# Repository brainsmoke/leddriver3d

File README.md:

# LED Driver for 3D sculptures based on an ESP32 with PSRAM + an STM32F0XX

# Design:

```
   programming &
  micropython REPL
         ||
     .--------.
     |  usb   |
     |   to   |  unified codebase       project specific firmware
     | serial |    /                            \
     '--------'   /                              \
         ||      /   standardized protocol        \
   .--------------.            |                  _____________.--
   |  ESP32-D0WD  |          (UART)              |             |-- multiple LED strands
   |   8M PSRAM   |-- 16bit/color LED frames --> |  STM32F0XX  |-- (temporal dithered)
   |  16M FLASH   |                              |_____________|--
   '--------------'                                            '--

```

# ESP Code `firmware/esp32/`

- Running micropython

- 60 FPS 16bit/color (48bit) animation with some routines written in C for speed.

- Animations use 3D-coordinates of the LEDs, as well as the direction they're pointing at

- Gamma correction & support for multiple LED orderings.

- Cached animation frames to prevent garbage collection hiccups

- Web interface (HTTPS capable, but no automatic cert. updates)

# STM32 Code `firmware/stm32/`

## Protocol

Sending a frame: `( [16 bit brightness]* [ FF FF FF F0 ] )*`

Brightness must be little endian integers in the (inclusive) range `[0 .. 0xFF00]`

`[ FF FF FF F0 ]` is an end of frame marker and allows the protocol to synchronize
in the event of an uneven number of bytes being written to the serial port

The firmware is completely agnostic about the color ordering.

Some of the following firmwares allow for tuning of the pulse interval:

`( [16 bit number]* [ FF FF FF F3 ] )*`

The given number is the number of cycles outputting a byte should take.
(Useful for increasing the FPS and thus improving temporal dithering.

## `dither16.bin`

Read in 16bit/color data in, drive 8 ws2812 LED strips in parallel

## `strip4.bin`

Read in 16bit/color data in, drive 4 ws2812 LED strips in parallel

## `strip5.bin`

Read in 16bit/color data in, drive 5 ws2812 LED strips in parallel,
Supports tuning the pulse interval.

## `relayball.bin`

Read in 16bit/color data in, drive 4 circuit-routed ws2812 LED meshes.
Small LED strands are connected through PADAUK based relay-chips
(`firmware/pdk/relay/`) that use in-band messages to build up routing
circuits.

## `uartball16.bin`

Drives up-to 8 busses with PADAUK based LED drivers which read 38400 baud
uart. `firmware/pdk/softpwm/`

##  `dither8.bin`

Older code using a different input protocol, reads 8bit/color data & transforms this to 16 bit colors
after gamma correction

# STM32 Tester code

## `jitter_timer.bin`

Tester for PADAUK ws2812 relay chips. `firmware/pdk/relay/`

Tests for functionality and measures the clock speed deviation (for binning).

## `timing_experiment.bin`

Dynamically adjust the `T1H` and `T1L` intervals from the ws2812 protocol to
test its limits.

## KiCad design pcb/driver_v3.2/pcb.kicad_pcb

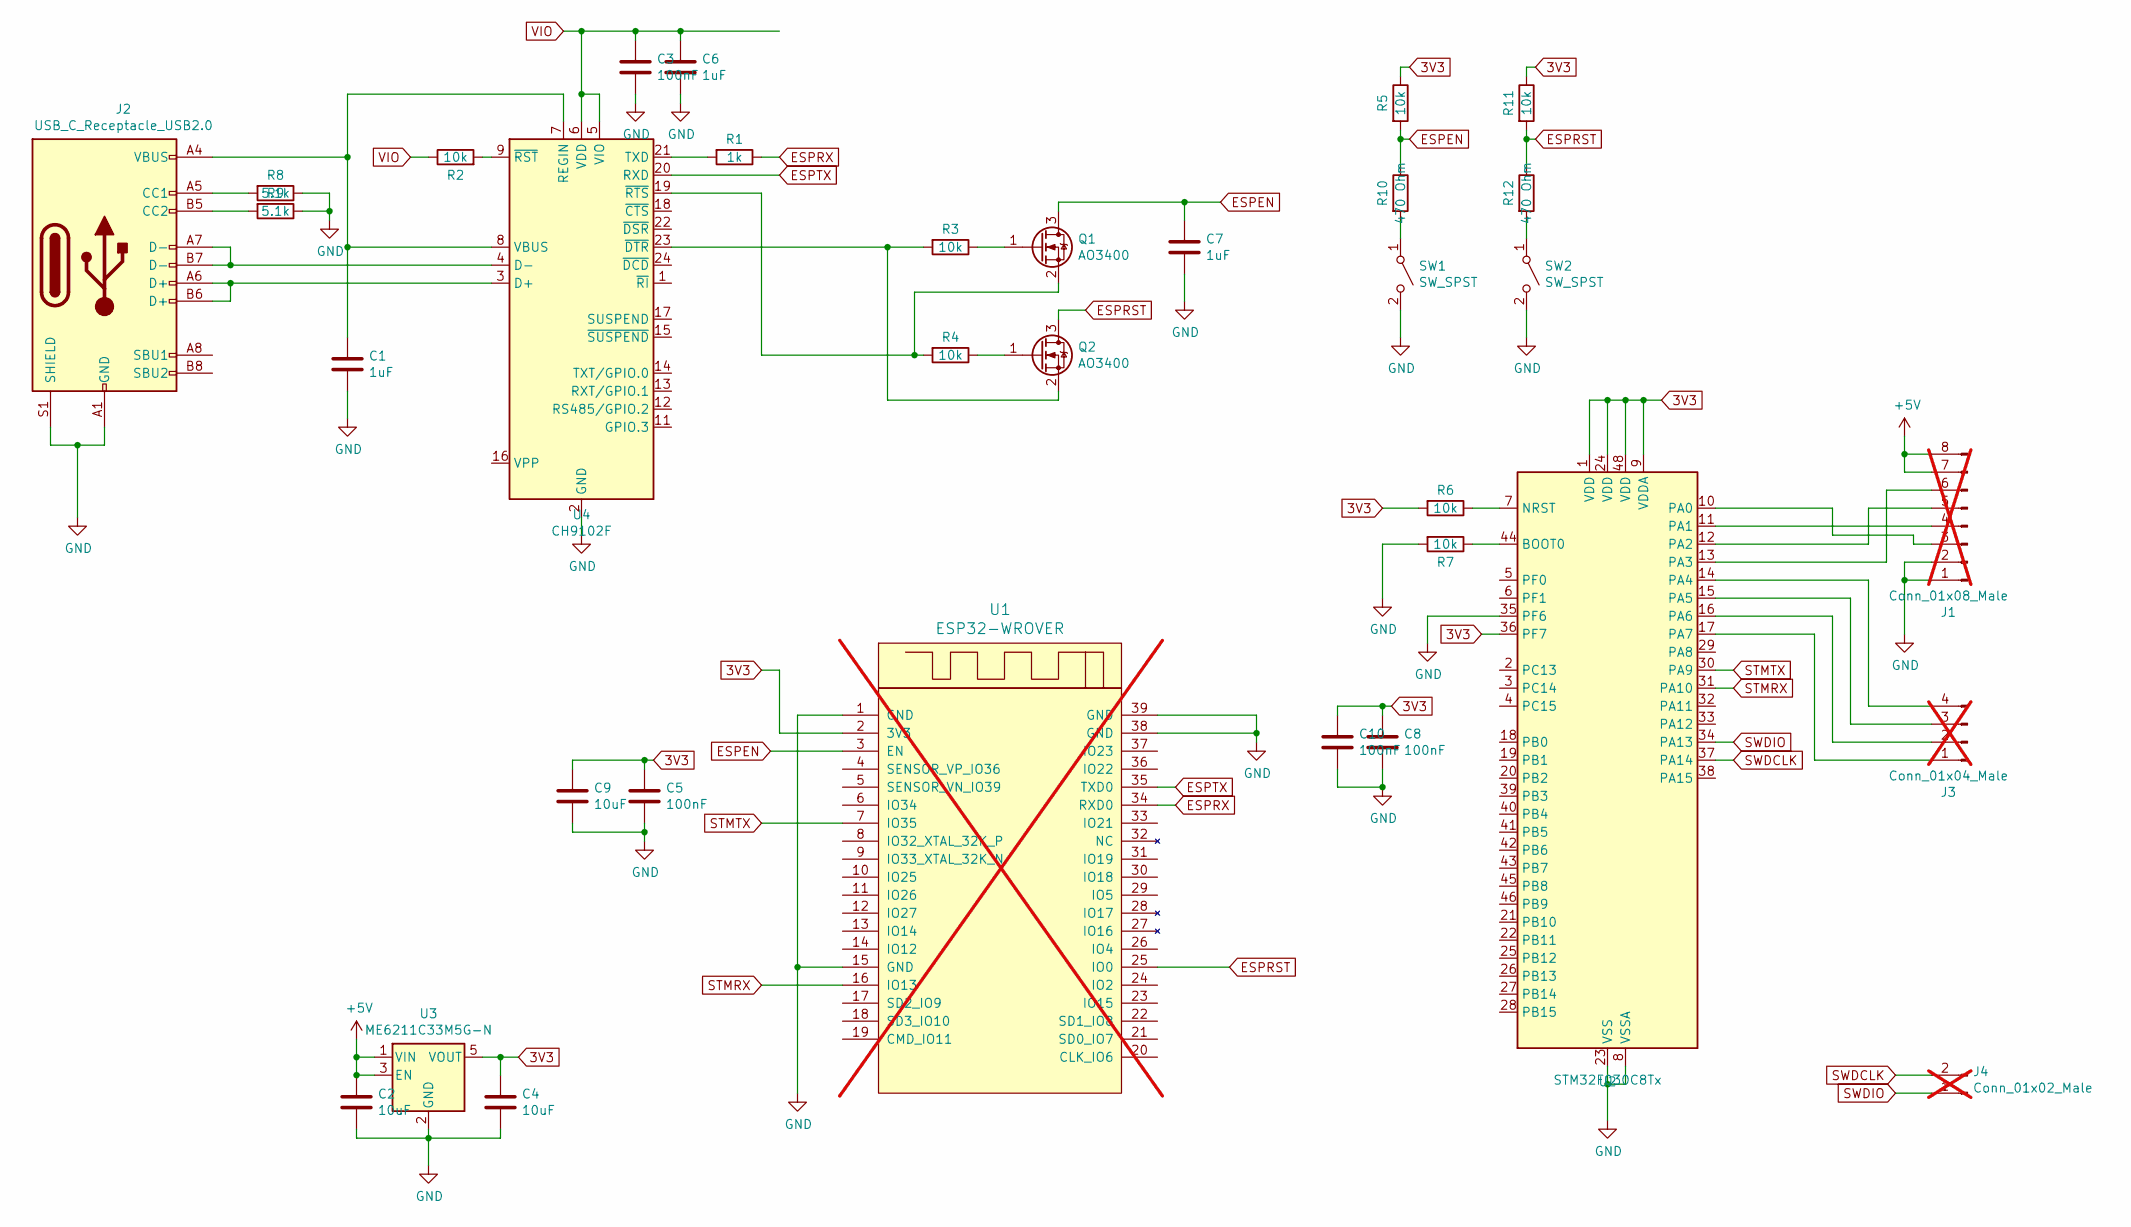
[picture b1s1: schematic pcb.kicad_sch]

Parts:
C1, C6, C7: 1uF; C_0402_1005Metric; LCSC C52923
C2, C4, C9: 10uF; C_0603_1608Metric; LCSC C19702
C3, C5, C8, C10: 100nF; C_0402_1005Metric; LCSC C1525
J1: Conn_01x08_Male; PinHeader_1x08_P2.54mm_Vertical; not fitted
J2: USB_C_Receptacle_USB2.0; USB_C_Receptacle_HRO_TYPE-C-31-M-12; LCSC C165948
J3: Conn_01x04_Male; PinHeader_1x04_P2.54mm_Vertical; not fitted
J4: Conn_01x02_Male; PinHeader_1x02_P2.54mm_Vertical; not fitted
Q1, Q2: AO3400; SOT-23; LCSC C20917
R1: 1k; R_0402_1005Metric; LCSC C11702
R2, R3, R4, R5, R6, R7, R11: 10k; R_0402_1005Metric; LCSC C25744
R8, R9: 5.1k; R_0402_1005Metric; LCSC C25905
R10, R12: 470 Ohm; R_0402_1005Metric; LCSC C25117
SW1, SW2: SW_SPST; SW_Push_1P1T_NO_CK_KMR2; LCSC C318893
U1: ESP32-WROVER; XCVR_ESP32-WROVER; not fitted
U2: STM32F030C8Tx; LQFP-48_7x7mm_P0.5mm; LCSC C23922
U3: ME6211C33M5G-N; SOT-23-5; LCSC C82942
U4: CH9102F; QFN-24-1EP_4x4mm_P0.5mm_EP2.6x2.6mm; LCSC C2858418

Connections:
3V3: C4.1, C5.1, C8.1, C9.1, C10.1, R5.1, R6.2, R11.1, U1.2 (3V3), U2.1 (VDD), U2.9 (VDDA), U2.24 (VDD), U2.36 (PF7), U2.48 (VDD), U3.5 (VOUT)
+5V: C2.1, J1.7, J1.8, U3.1 (VIN), U3.3 (EN)
ESPEN: C7.1, Q1.3 (D), R5.2, R10.1, U1.3 (EN)
ESPRST: Q2.3 (D), R11.2, R12.1, U1.25 (IO0)
ESPRX: R1.1, U1.34 (RXD0)
ESPTX: U1.35 (TXD0), U4.20 (RXD)
GND: C1.2, C2.2, C3.2, C4.2, C5.2, C6.2, C7.2, C8.2, C9.2, C10.2, J1.1, J1.2, J2.A1 (GND), J2.A12 (GND), J2.B1 (GND), J2.B12 (GND), J2.S1 (SHIELD), R7.2, R8.1, R9.1, SW1.2 (B), SW2.2 (B), U1.1 (GND), U1.15 (GND), U1.38 (GND), U1.39 (GND), U2.8 (VSSA), U2.23 (VSS), U2.35 (PF6), U2.47 (VSS), U3.2 (GND), U4.2 (GND), U4.25 (GND)
unnamed: J1.3, U2.10 (PA0)
unnamed: J1.4, U2.11 (PA1)
unnamed: J1.5, U2.12 (PA2)
unnamed: J1.6, U2.13 (PA3)
unnamed: J2.A5 (CC1), R8.2
unnamed: J2.B5 (CC2), R9.2
unnamed: J3.1, U2.17 (PA7)
unnamed: J3.2, U2.16 (PA6)
unnamed: J3.3, U2.15 (PA5)
unnamed: J3.4, U2.14 (PA4)
unnamed: Q1.1 (G), R3.1
unnamed: Q1.2 (S), R4.2, U4.19 (~RTS)
unnamed: Q2.1 (G), R4.1
unnamed: Q2.2 (S), R3.2, U4.23 (~DTR)
unnamed: R10.2, SW1.1 (A)
unnamed: R12.2, SW2.1 (A)
unnamed: R7.1, U2.44 (BOOT0)
unnamed: R6.1, U2.7 (NRST)
unnamed: J2.A6 (D+), J2.B6 (D+), U4.3 (D+)
unnamed: J2.A7 (D-), J2.B7 (D-), U4.4 (D-)
unnamed: C1.1, J2.A4 (VBUS), J2.A9 (VBUS), J2.B4 (VBUS), J2.B9 (VBUS), U4.7 (REGIN), U4.8 (VBUS)
unnamed: R1.2, U4.21 (TXD)
unnamed: R2.2, U4.9 (~RST)
STMRX: U1.16 (IO13), U2.31 (PA10)
STMTX: U1.7 (IO35), U2.30 (PA9)
SWDCLK: J4.2, U2.37 (PA14)
SWDIO: J4.1, U2.34 (PA13)
VIO: C3.1, C6.1, R2.1, U4.5 (VIO), U4.6 (VDD)

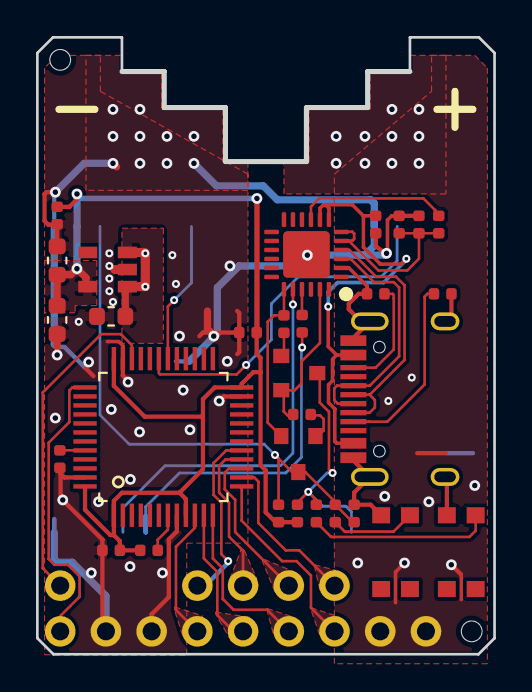
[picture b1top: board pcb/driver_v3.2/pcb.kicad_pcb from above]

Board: 4 copper layers, 25.4 x 34.3 mm, 34 parts (1 on the bottom side), 35 nets.

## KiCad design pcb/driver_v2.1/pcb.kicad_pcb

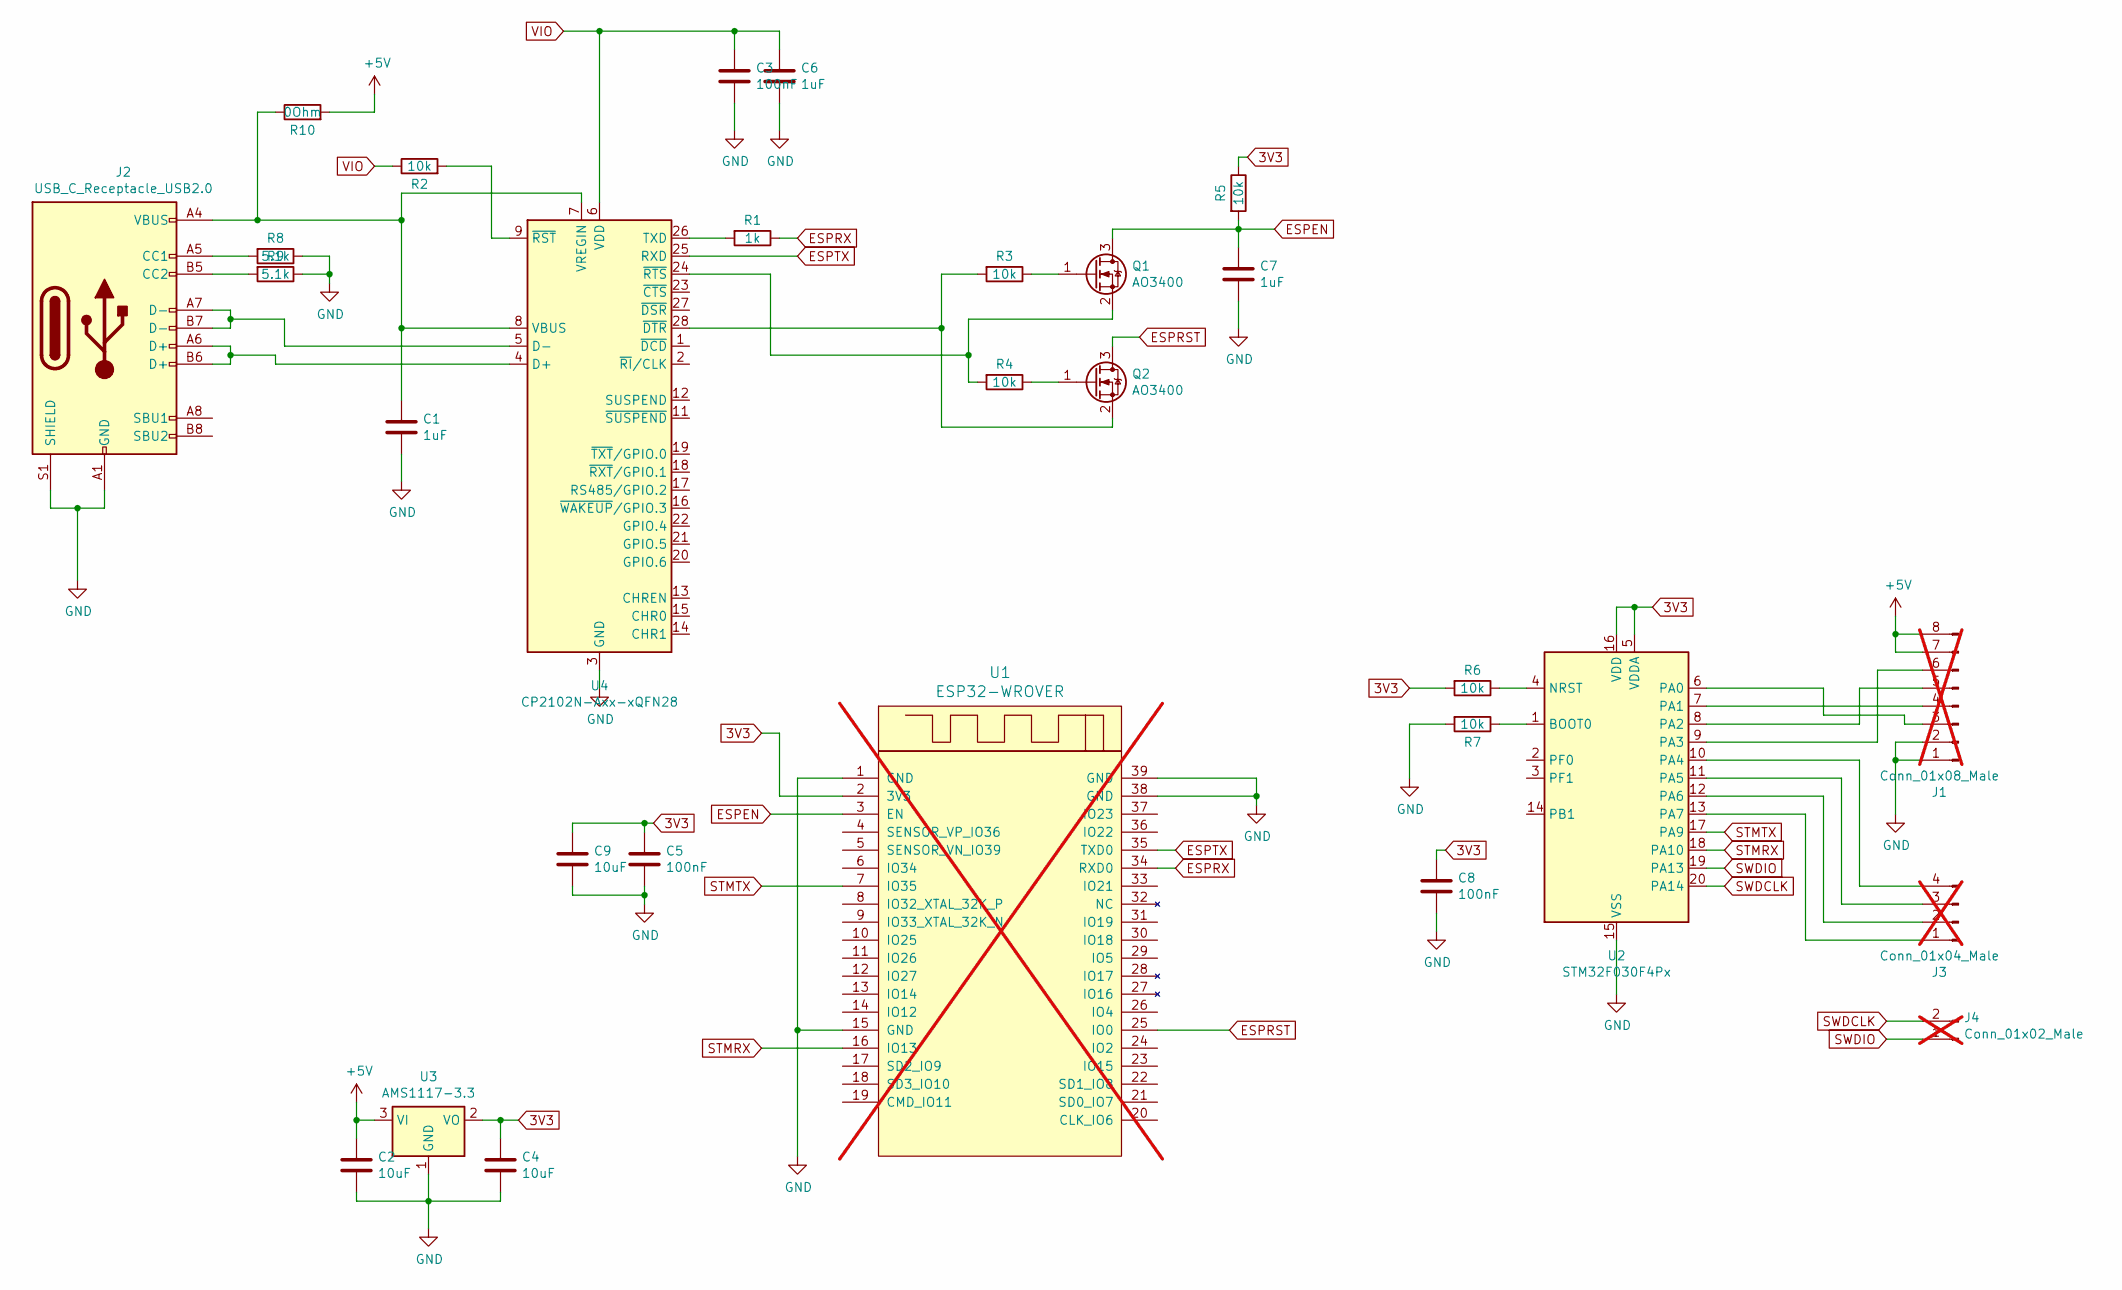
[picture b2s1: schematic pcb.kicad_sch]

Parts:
C1, C6, C7: 1uF; C_0603_1608Metric; LCSC C15849
C2, C4: 10uF; C_0603_1608Metric; LCSC C15850
C3, C5, C8: 100nF; C_0603_1608Metric; LCSC C14663
C9: 10uF; C_0603_1608Metric; LCSC C19702
J1: Conn_01x08_Male; PinHeader_1x08_P2.54mm_Vertical; not fitted
J2: USB_C_Receptacle_USB2.0; USB_C_Receptacle_HRO_TYPE-C-31-M-12; LCSC C165948
J3: Conn_01x04_Male; PinHeader_1x04_P2.54mm_Vertical; not fitted
J4: Conn_01x02_Male; PinHeader_1x02_P2.54mm_Vertical; not fitted
Q1, Q2: AO3400; SOT-23; LCSC C20917
R1: 1k; R_0603_1608Metric_nolabel; LCSC C21190
R2, R3, R4, R5, R6, R7: 10k; R_0603_1608Metric_nolabel; LCSC C25804
R8, R9: 5.1k; R_0603_1608Metric_nolabel; LCSC C23186
R10: 0Ohm; R_0603_1608Metric_nolabel; LCSC C25804
U1: ESP32-WROVER; XCVR_ESP32-WROVER; not fitted
U2: STM32F030F4Px; TSSOP-20_4.4x6.5mm_P0.65mm; LCSC C89040
U3: AMS1117-3.3; SOT-223-3_TabPin2; LCSC C6186
U4: CP2102N-Axx-xQFN28; QFN-28-1EP_5x5mm_P0.5mm_EP3.35x3.35mm; LCSC C6568

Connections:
3V3: C4.1, C5.1, C8.1, C9.1, R5.1, R6.2, U1.2 (3V3), U2.5 (VDDA), U2.16 (VDD), U3.2 (VO)
+5V: C2.1, J1.7, J1.8, R10.2, U3.3 (VI)
ESPEN: C7.1, Q1.3 (D), R5.2, U1.3 (EN)
ESPRST: Q2.3 (D), U1.25 (IO0)
ESPRX: R1.1, U1.34 (RXD0)
ESPTX: U1.35 (TXD0), U4.25 (RXD)
GND: C1.2, C2.2, C3.2, C4.2, C5.2, C6.2, C7.2, C8.2, C9.2, J1.1, J1.2, J2.A1 (GND), J2.A12 (GND), J2.B1 (GND), J2.B12 (GND), J2.S1 (SHIELD), R7.2, R8.1, R9.1, U1.1 (GND), U1.15 (GND), U1.38 (GND), U1.39 (GND), U2.15 (VSS), U3.1 (GND), U4.3 (GND), U4.29 (GND)
unnamed: J1.3, U2.6 (PA0)
unnamed: J1.4, U2.7 (PA1)
unnamed: J1.5, U2.8 (PA2)
unnamed: J1.6, U2.9 (PA3)
unnamed: J2.A5 (CC1), R8.2
unnamed: J2.B5 (CC2), R9.2
unnamed: J3.1, U2.13 (PA7)
unnamed: J3.2, U2.12 (PA6)
unnamed: J3.3, U2.11 (PA5)
unnamed: J3.4, U2.10 (PA4)
unnamed: Q1.1 (G), R3.1
unnamed: Q1.2 (S), R4.2, U4.24 (~RTS)
unnamed: Q2.1 (G), R4.1
unnamed: Q2.2 (S), R3.2, U4.28 (~DTR)
unnamed: R7.1, U2.1 (BOOT0)
unnamed: R6.1, U2.4 (NRST)
unnamed: J2.A6 (D+), J2.B6 (D+), U4.4 (D+)
unnamed: J2.A7 (D-), J2.B7 (D-), U4.5 (D-)
unnamed: R1.2, U4.26 (TXD)
unnamed: C1.1, J2.A4 (VBUS), J2.A9 (VBUS), J2.B4 (VBUS), J2.B9 (VBUS), R10.1, U4.7 (VREGIN), U4.8 (VBUS)
unnamed: R2.2, U4.9 (~RST)
STMRX: U1.16 (IO13), U2.18 (PA10)
STMTX: U1.7 (IO35), U2.17 (PA9)
SWDCLK: J4.2, U2.20 (PA14)
SWDIO: J4.1, U2.19 (PA13)
VIO: C3.1, C6.1, R2.1, U4.6 (VDD)

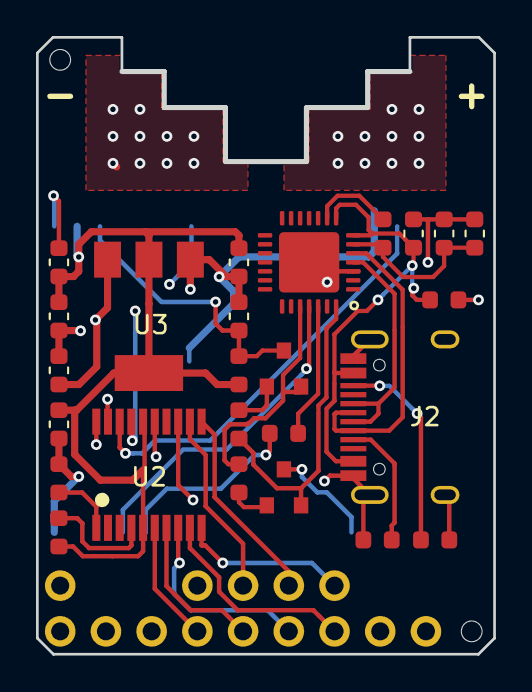
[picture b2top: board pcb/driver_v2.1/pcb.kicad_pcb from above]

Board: 4 copper layers, 25.4 x 34.3 mm, 29 parts (1 on the bottom side), 33 nets.

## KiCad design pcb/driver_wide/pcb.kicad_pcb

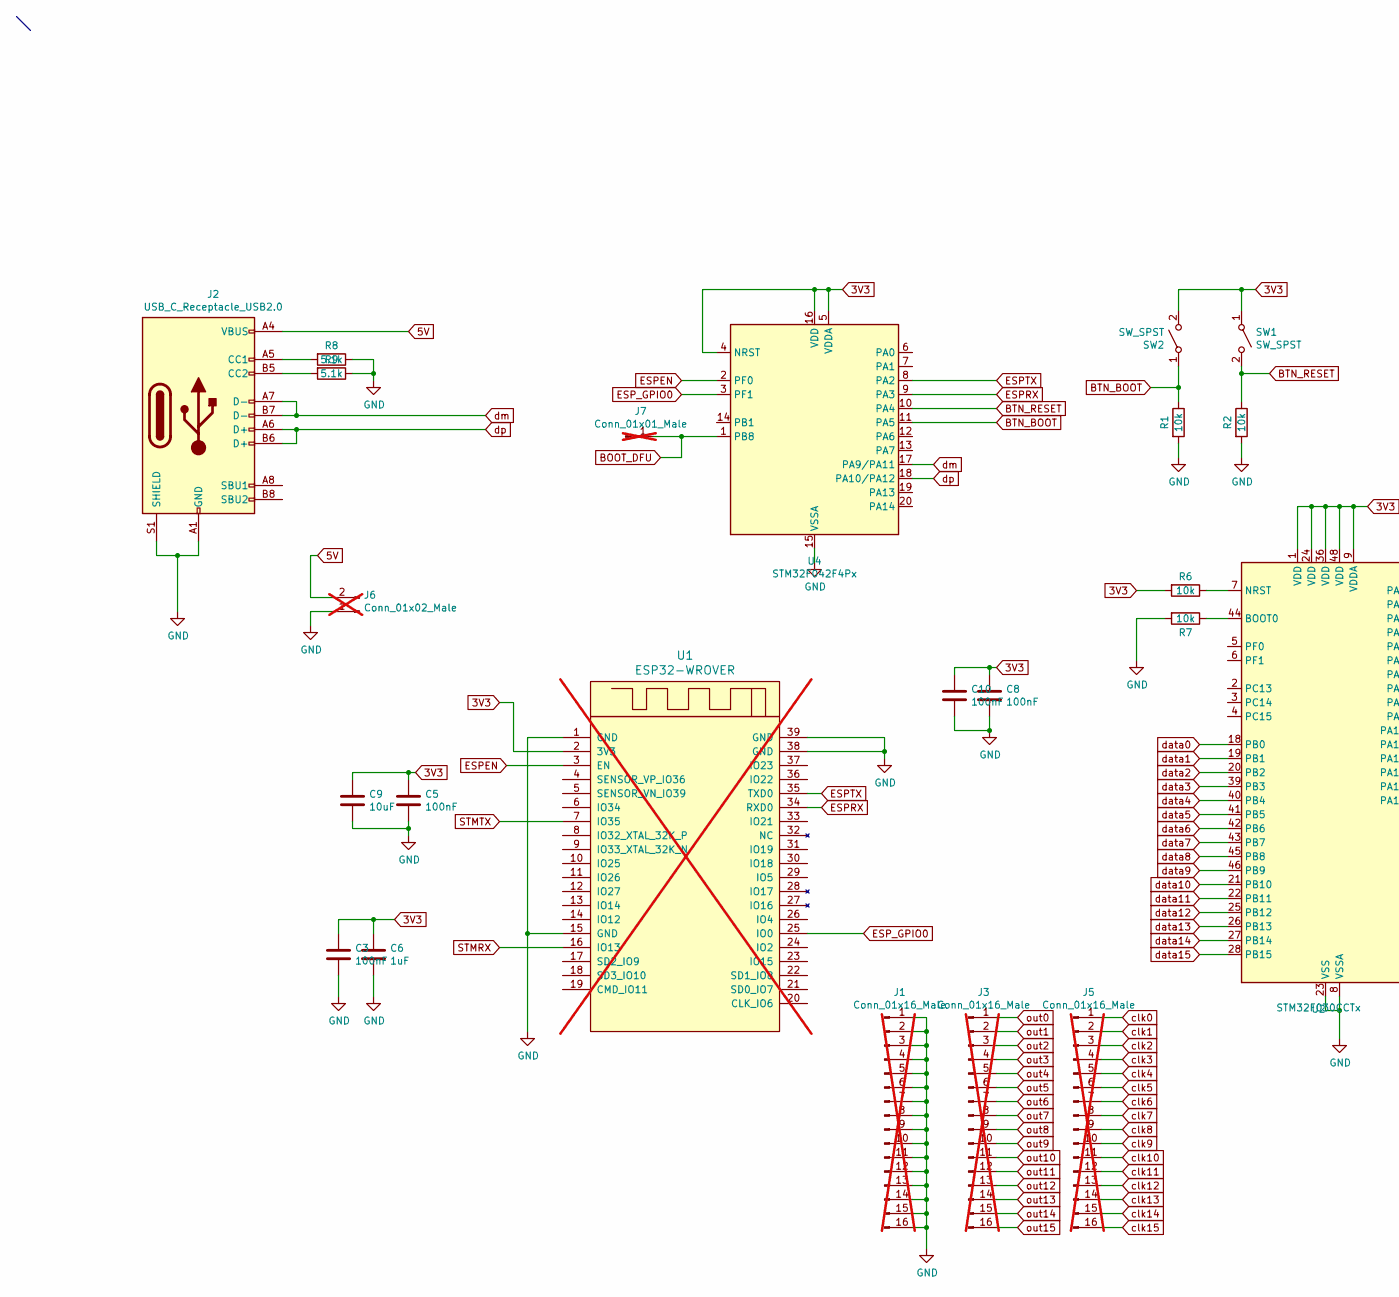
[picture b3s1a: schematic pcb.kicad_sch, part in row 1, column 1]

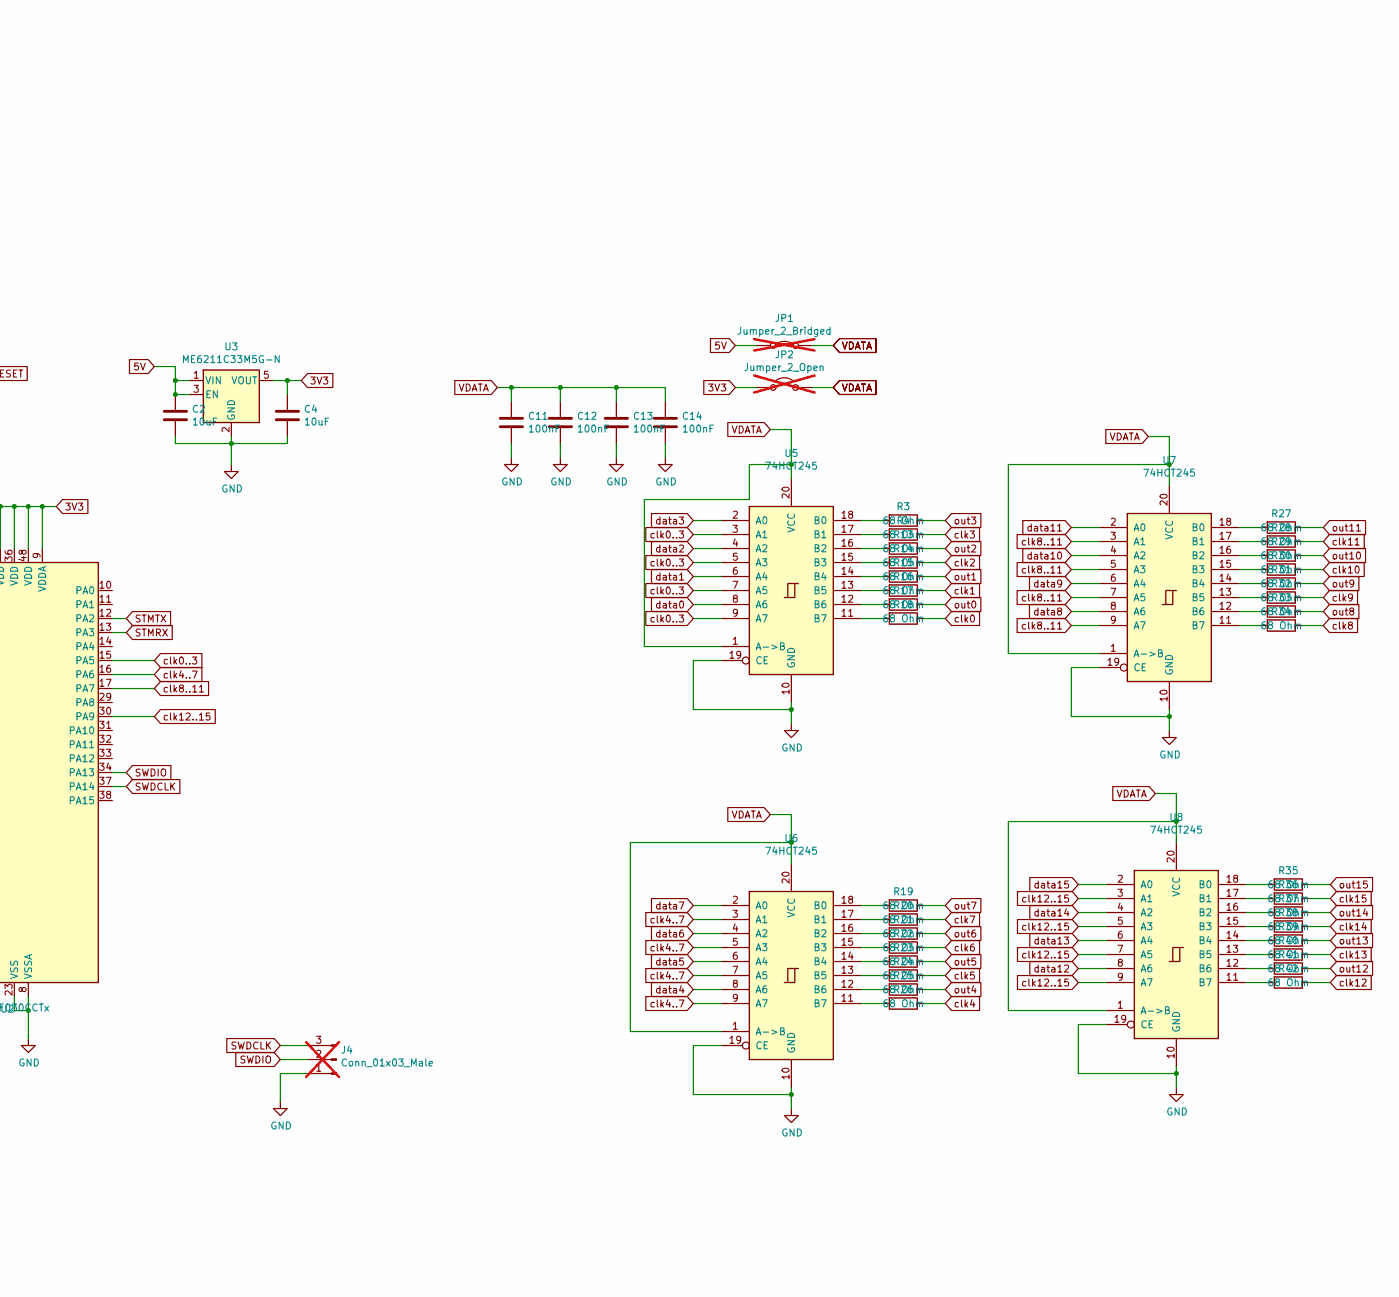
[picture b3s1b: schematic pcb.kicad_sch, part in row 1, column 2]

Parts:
C2, C4, C9: 10uF; C_0603_1608Metric; LCSC C19702
C3, C5, C8, C10: 100nF; C_0402_1005Metric; LCSC C1525
C6: 1uF; C_0402_1005Metric; LCSC C52923
C11, C12, C13, C14: 100nF; C_0402_1005Metric; LCSC C19702
J1, J3, J5: Conn_01x16_Male; PinHeader_1x16_P2.54mm_Vertical; not fitted
J2: USB_C_Receptacle_USB2.0; USB_C_Receptacle_HRO_TYPE-C-31-M-12; LCSC C165948
J4: Conn_01x03_Male; PinHeader_1x03_P2.54mm_Vertical; not fitted
J6: Conn_01x02_Male; PinHeader_1x02_P2.54mm_Vertical; not fitted
J7: Conn_01x01_Male; PinHeader_1x01_P2.54mm_Vertical; not fitted
JP1: Jumper_2_Bridged; SolderJumper-2_P1.3mm_Bridged_Pad1.0x1.5mm; not fitted
JP2: Jumper_2_Open; SolderJumper-2_P1.3mm_Open_Pad1.0x1.5mm; not fitted
R1, R2, R6, R7: 10k; R_0402_1005Metric; LCSC C25744
R3, R4, R13, R14, R15, R16, R17, R18, R19, R20, R21, R22, R23, R24, R25, R26, R27, R28, R29, R30, R31, R32, R33, R34, R35, R36, R37, R38, R39, R40, R41, R42: 68 Ohm; R_0402_1005Metric; LCSC C25744
R8, R9: 5.1k; R_0402_1005Metric; LCSC C25905
SW1, SW2: SW_SPST; SW_Push_1P1T_NO_CK_KMR2; LCSC C318893
U1: ESP32-WROVER; XCVR_ESP32-WROVER; not fitted
U2: STM32F030CCTx; LQFP-48_7x7mm_P0.5mm; LCSC C81787
U3: ME6211C33M5G-N; SOT-23-5; LCSC C82942
U4: STM32F042F4Px; TSSOP-20_4.4x6.5mm_P0.65mm; LCSC C81000
U5, U6, U7, U8: 74HCT245; TSSOP-20_4.4x6.5mm_P0.65mm; LCSC C5980

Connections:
3V3: C3.1, C4.1, C5.1, C6.1, C8.1, C9.1, C10.1, JP2.1 (A), R6.2, SW1.1 (A), SW2.2 (B), U1.2 (3V3), U2.1 (VDD), U2.9 (VDDA), U2.24 (VDD), U2.36 (VDD), U2.48 (VDD), U3.5 (VOUT), U4.4 (NRST), U4.5 (VDDA), U4.16 (VDD)
5V: C2.1, J2.A4 (VBUS), J2.A9 (VBUS), J2.B4 (VBUS), J2.B9 (VBUS), J6.2, JP1.1 (A), U3.1 (VIN), U3.3 (EN)
BOOT_DFU: J7.1, U4.1 (PB8)
BTN_BOOT: R1.1, SW2.1 (A), U4.11 (PA5)
BTN_RESET: R2.1, SW1.2 (B), U4.10 (PA4)
ESPEN: U1.3 (EN), U4.2 (PF0)
ESPRX: U1.34 (RXD0), U4.9 (PA3)
ESPTX: U1.35 (TXD0), U4.8 (PA2)
ESP_GPIO0: U1.25 (IO0), U4.3 (PF1)
GND: C2.2, C3.2, C4.2, C5.2, C6.2, C8.2, C9.2, C10.2, C11.2, C12.2, C13.2, C14.2, J1.1, J1.2, J1.3, J1.4, J1.5, J1.6, J1.7, J1.8, J1.9, J1.10, J1.11, J1.12, J1.13, J1.14, J1.15, J1.16, J2.A1 (GND), J2.A12 (GND), J2.B1 (GND), J2.B12 (GND), J2.S1 (SHIELD), J4.1, J6.1, R1.2, R2.2, R7.2, R8.1, R9.1, U1.1 (GND), U1.15 (GND), U1.38 (GND), U1.39 (GND), U2.8 (VSSA), U2.23 (VSS), U2.35 (VSS), U2.47 (VSS), U3.2 (GND), U4.15 (VSSA), U5.10 (GND), U5.19 (CE), U6.10 (GND), U6.19 (CE), U7.10 (GND), U7.19 (CE), U8.10 (GND), U8.19 (CE)
unnamed: J2.A5 (CC1), R8.2
unnamed: J2.B5 (CC2), R9.2
unnamed: R7.1, U2.44 (BOOT0)
unnamed: R6.1, U2.7 (NRST)
unnamed: R3.2, U5.18 (B0)
unnamed: R4.2, U5.17 (B1)
unnamed: R13.2, U5.16 (B2)
unnamed: R14.2, U5.15 (B3)
unnamed: R15.2, U5.14 (B4)
unnamed: R16.2, U5.13 (B5)
unnamed: R17.2, U5.12 (B6)
unnamed: R18.2, U5.11 (B7)
unnamed: R19.2, U6.18 (B0)
unnamed: R20.2, U6.17 (B1)
unnamed: R21.2, U6.16 (B2)
unnamed: R22.2, U6.15 (B3)
unnamed: R23.2, U6.14 (B4)
unnamed: R24.2, U6.13 (B5)
unnamed: R25.2, U6.12 (B6)
unnamed: R26.2, U6.11 (B7)
unnamed: R27.2, U7.18 (B0)
unnamed: R28.2, U7.17 (B1)
unnamed: R29.2, U7.16 (B2)
unnamed: R30.2, U7.15 (B3)
unnamed: R31.2, U7.14 (B4)
unnamed: R32.2, U7.13 (B5)
unnamed: R33.2, U7.12 (B6)
unnamed: R34.2, U7.11 (B7)
unnamed: R35.2, U8.18 (B0)
unnamed: R36.2, U8.17 (B1)
unnamed: R37.2, U8.16 (B2)
unnamed: R38.2, U8.15 (B3)
unnamed: R39.2, U8.14 (B4)
unnamed: R40.2, U8.13 (B5)
unnamed: R41.2, U8.12 (B6)
unnamed: R42.2, U8.11 (B7)
STMRX: U1.16 (IO13), U2.13 (PA3)
STMTX: U1.7 (IO35), U2.12 (PA2)
SWDCLK: J4.3, U2.37 (PA14)
SWDIO: J4.2, U2.34 (PA13)
VDATA: C11.1, C12.1, C13.1, C14.1, JP1.2 (B), JP2.2 (B), U5.1 (A->B), U5.20 (VCC), U6.1 (A->B), U6.20 (VCC), U7.1 (A->B), U7.20 (VCC), U8.1 (A->B), U8.20 (VCC)
clk0: J5.1, R18.1
clk0..3: U2.15 (PA5), U5.3 (A1), U5.5 (A3), U5.7 (A5), U5.9 (A7)
clk1: J5.2, R16.1
clk2: J5.3, R14.1
clk3: J5.4, R4.1
clk4: J5.5, R26.1
clk4..7: U2.16 (PA6), U6.3 (A1), U6.5 (A3), U6.7 (A5), U6.9 (A7)
clk5: J5.6, R24.1
clk6: J5.7, R22.1
clk7: J5.8, R20.1
clk8: J5.9, R34.1
clk8..11: U2.17 (PA7), U7.3 (A1), U7.5 (A3), U7.7 (A5), U7.9 (A7)
clk9: J5.10, R32.1
clk10: J5.11, R30.1
clk11: J5.12, R28.1
clk12: J5.13, R42.1
clk12..15: U2.30 (PA9), U8.3 (A1), U8.5 (A3), U8.7 (A5), U8.9 (A7)
clk13: J5.14, R40.1
clk14: J5.15, R38.1
clk15: J5.16, R36.1
data0: U2.18 (PB0), U5.8 (A6)
data1: U2.19 (PB1), U5.6 (A4)
data2: U2.20 (PB2), U5.4 (A2)
data3: U2.39 (PB3), U5.2 (A0)
data4: U2.40 (PB4), U6.8 (A6)
data5: U2.41 (PB5), U6.6 (A4)
data6: U2.42 (PB6), U6.4 (A2)
data7: U2.43 (PB7), U6.2 (A0)
data8: U2.45 (PB8), U7.8 (A6)
data9: U2.46 (PB9), U7.6 (A4)
data10: U2.21 (PB10), U7.4 (A2)
data11: U2.22 (PB11), U7.2 (A0)
data12: U2.25 (PB12), U8.8 (A6)
data13: U2.26 (PB13), U8.6 (A4)
data14: U2.27 (PB14), U8.4 (A2)
data15: U2.28 (PB15), U8.2 (A0)
dm: J2.A7 (D-), J2.B7 (D-), U4.17 (PA9/PA11)
dp: J2.A6 (D+), J2.B6 (D+), U4.18 (PA10/PA12)
out0: J3.1, R17.1
out1: J3.2, R15.1
out2: J3.3, R13.1
out3: J3.4, R3.1
out4: J3.5, R25.1
out5: J3.6, R23.1
out6: J3.7, R21.1
out7: J3.8, R19.1
out8: J3.9, R33.1
out9: J3.10, R31.1
out10: J3.11, R29.1
out11: J3.12, R27.1
out12: J3.13, R41.1
out13: J3.14, R39.1
out14: J3.15, R37.1
out15: J3.16, R35.1

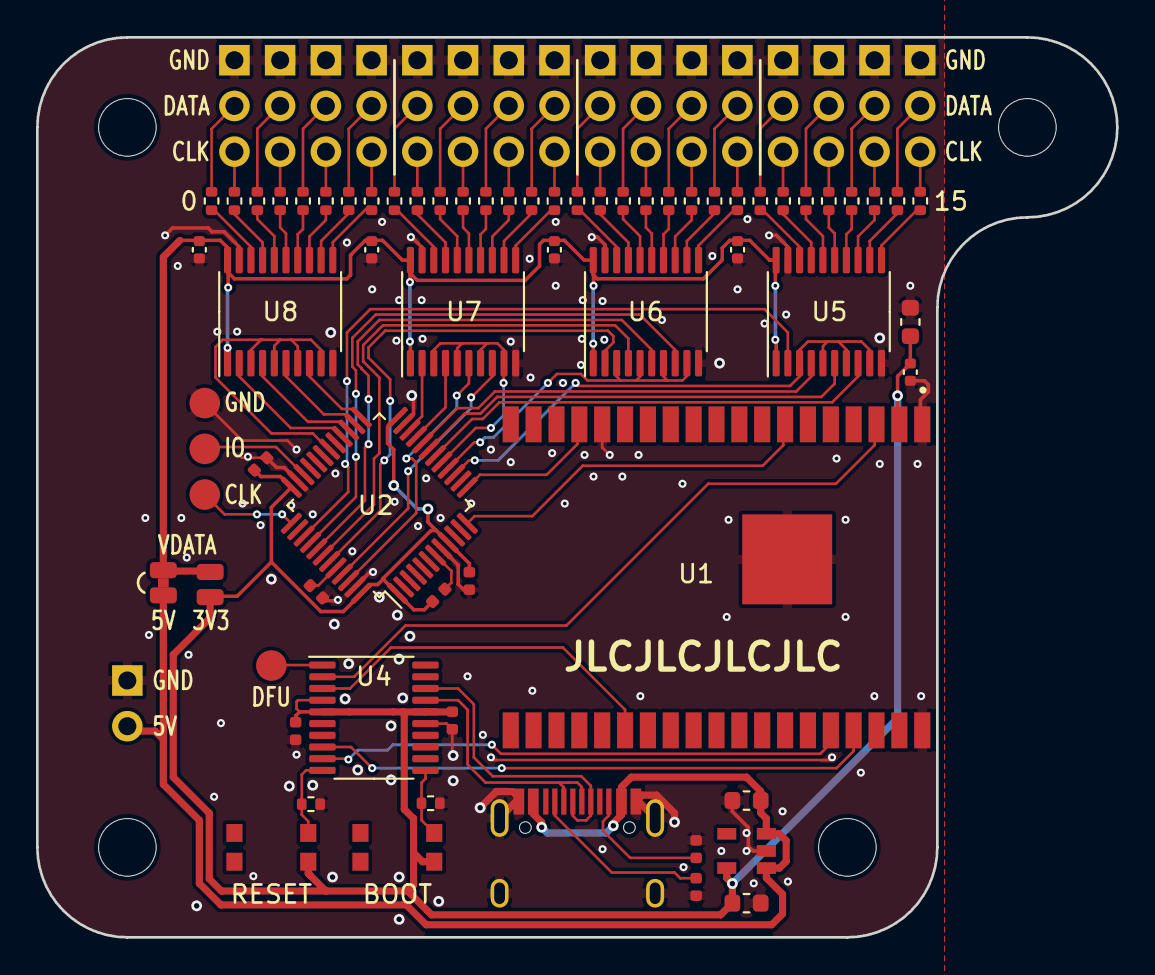
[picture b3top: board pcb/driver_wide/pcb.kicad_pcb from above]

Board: 2 copper layers, 60.0 x 50.0 mm, 69 parts (0 on the bottom side), 105 nets.

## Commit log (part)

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2025-09-30 switch LED strips to match chiral_sphere:distr_main & driver_compact PCBs
2025-10-28 allow spaces in network config (oops) :-)
2025-12-22 add stm32 driver for the original polyhedrone (RGB led order)
2026-01-09 repository rename
2026-01-09 fix name of renamed repo
2026-01-09 design asciiart
2026-02-25 add great circles 'wiring' diagram
2026-04-29 update Makefile / production file generator script
